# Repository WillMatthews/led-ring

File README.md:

# LED Ring Board

This board is designed to place a ring of LEDs around a 30mm cage system.
Power it through a SMA connector, and place whatever 3mm LEDs you want on the board.
Choice of resistors is up to you, but I recommend you choose a good operating point (see datasheets, and compare with your power supply).

## Board
The board is a torus.

## Mount
A 3D printed mount is provided to attach the board to a 30mm cage system.

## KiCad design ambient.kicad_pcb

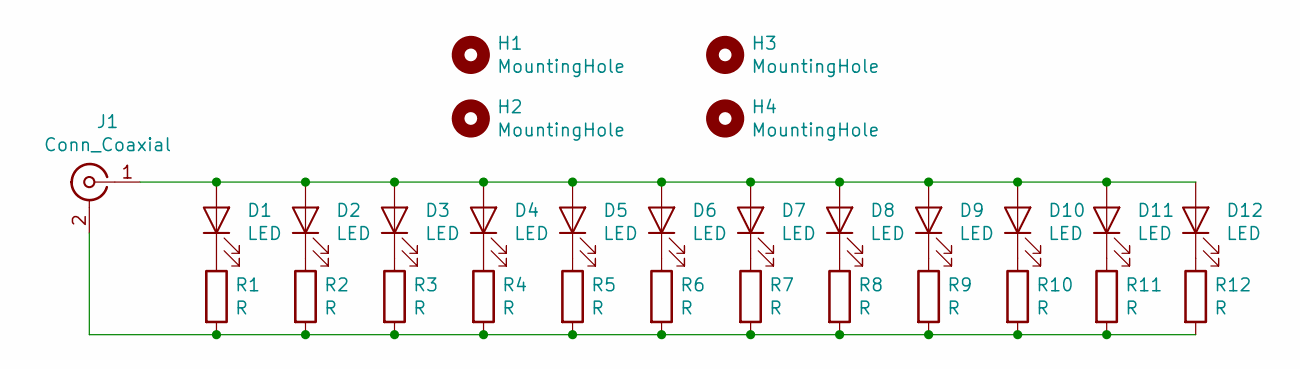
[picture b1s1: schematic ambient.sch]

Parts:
D1, D2, D3, D4, D5, D6, D7, D8, D9, D10, D11, D12: LED; LED_D3.0mm
H1, H2, H3, H4: MountingHole; MountingHole_3.2mm_M3_DIN965_Pad
J1: Conn_Coaxial; SMA_Amphenol_132289_EdgeMount
R1, R2, R3, R4, R5, R6, R7, R8, R9, R10, R11, R12: R; R_0805_2012Metric_Pad1.15x1.40mm_HandSolder

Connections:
unnamed: D1.1 (K), R1.1
unnamed: D1.2 (A), D2.2 (A), D3.2 (A), D4.2 (A), D5.2 (A), D6.2 (A), D7.2 (A), D8.2 (A), D9.2 (A), D10.2 (A), D11.2 (A), D12.2 (A), J1.1 (In)
unnamed: D2.1 (K), R2.1
unnamed: D3.1 (K), R3.1
unnamed: D4.1 (K), R4.1
unnamed: D5.1 (K), R5.1
unnamed: D6.1 (K), R6.1
unnamed: D7.1 (K), R7.1
unnamed: D8.1 (K), R8.1
unnamed: D9.1 (K), R9.1
unnamed: D10.1 (K), R10.1
unnamed: D11.1 (K), R11.1
unnamed: D12.1 (K), R12.1
unnamed: J1.2 (Ext), R1.2, R2.2, R3.2, R4.2, R5.2, R6.2, R7.2, R8.2, R9.2, R10.2, R11.2, R12.2

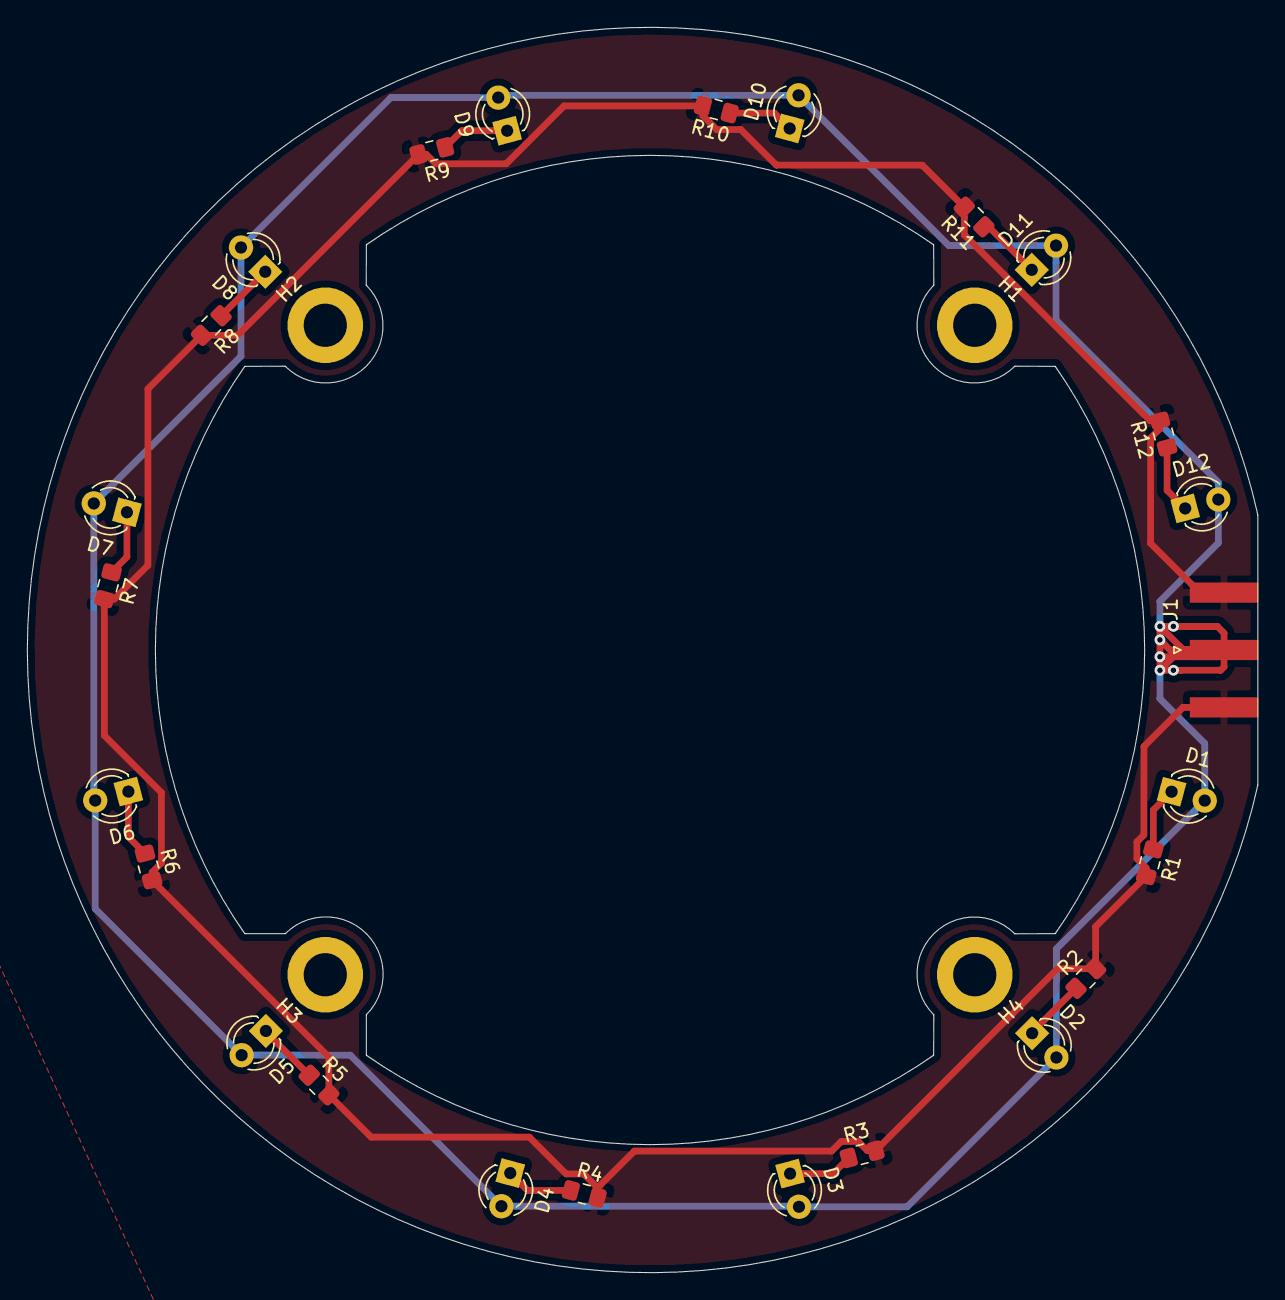
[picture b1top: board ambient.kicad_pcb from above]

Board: 2 copper layers, 91.1 x 92.2 mm, 29 parts (0 on the bottom side), 14 nets.

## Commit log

2024-04-06 led ring board
2024-04-06 readme
2024-04-06 Create LICENSE
